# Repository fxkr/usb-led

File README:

USB-RGB-LED
===========

A very simple + cheap + tiny USB-controllable RGB-LED.

Author: Felix Kaiser <felix.kaiser@fxkr.net>
License: GPLv2/GPLv3 (your choice)

Components:

- Board
- Firmware
- Linux tool

We use USB VID/PID f0ss:49d9 (screw you, USB-IF).

Thanks
------

This project is based on:

- Objective Developments V-USB (GPLv2/v3)
  http://www.obdev.at/products/vusb
- Micronucleus' RC Oscillator calibration routine (GPLv2/v3)
  https://github.com/micronucleus/micronucleus/blob/master/firmware/osccalASM.S
- libusb (LGPLv2.1 or later)
  http://libusb.info/
- SparkFuns Eagle Libraries (CC BY-SA 3.0)
  https://github.com/sparkfun/SparkFun-Eagle-Libraries

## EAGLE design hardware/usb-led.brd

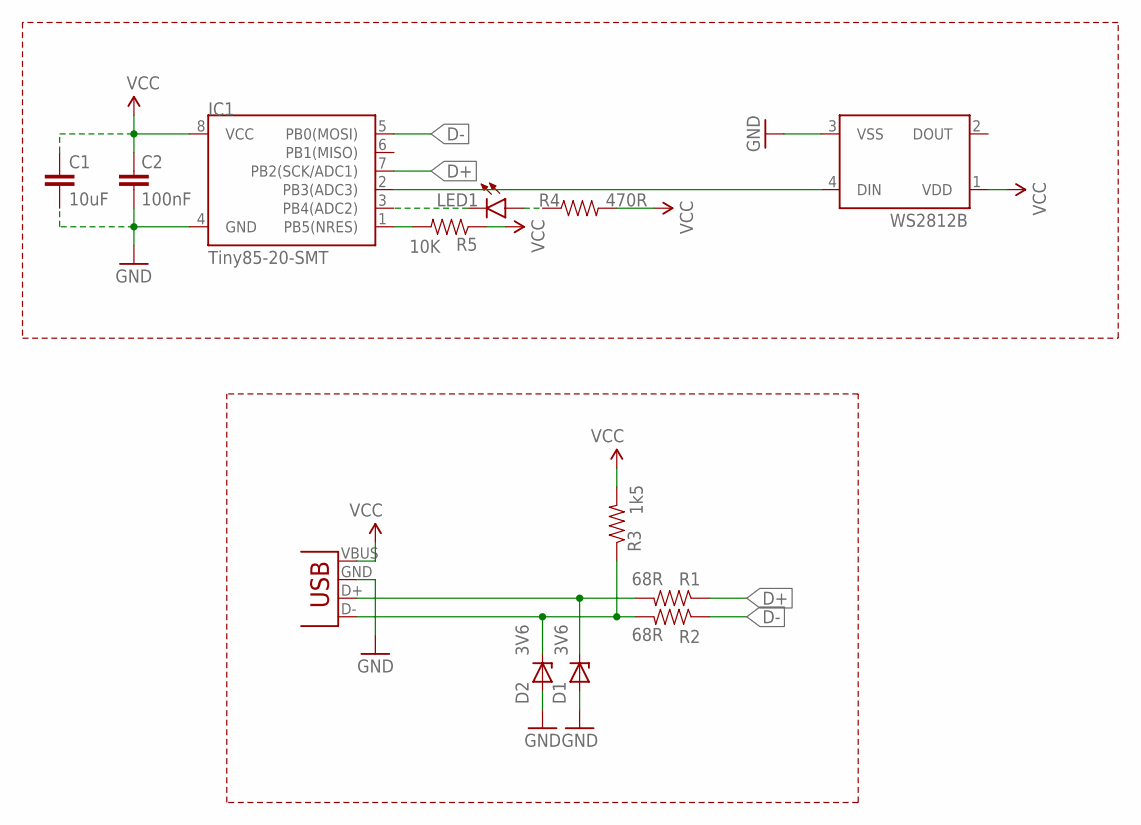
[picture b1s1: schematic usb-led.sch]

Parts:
C1: 10uF; C0805
C2: 100nF; 0805
D1, D2: 3V6; ZD0603
IC1: Tiny85-20-SMT; SO08-EIAJ
LED1: LED0603; LED-0603
R1, R2: 68R; 0603-RES
R3: 1k5; 0603-RES
R4: 470R; 0603-RES
R5: 10K; 0603-RES
USB: USB-A-H
WS2812B: WS2812B

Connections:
C10: IC1.1 (PB5(NRES)), R5.2
D+: IC1.7 (PB2(SCK/ADC1)), R1.1
D-: IC1.5 (PB0(MOSI)), R2.1
DIN: IC1.2 (PB3(ADC3)), WS2812B.4 (DIN)
EXT_D+: D1.K (C), R1.2, USB.D+ (D-)
EXT_D-: D2.K (C), R2.2, R3.1, USB.D- (D+)
GND: C1.2, C2.2, D1.A, D2.A, IC1.4 (GND), USB.GND (VBUS), WS2812B.3 (VSS)
unnamed: IC1.3 (PB4(ADC2)), LED1.C
unnamed: LED1.A, R4.1
VCC: C1.1, C2.1, IC1.8 (VCC), R3.2, R4.2, R5.1, USB.VBUS (GND), WS2812B.1 (VDD)

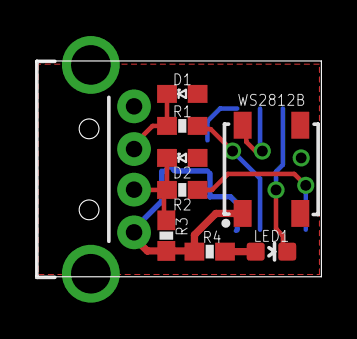
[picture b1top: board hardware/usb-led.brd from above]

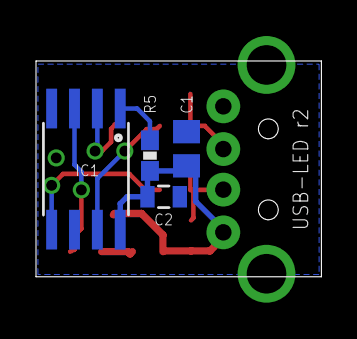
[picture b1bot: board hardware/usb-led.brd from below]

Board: 2 copper layers, 15.9 x 12.0 mm, 13 parts (4 on the bottom side), 10 nets.

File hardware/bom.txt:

Part     Value    Package     Digikey      Qty  Price
IC1      Attiny8  8-SOIC      ATTINY85-20   1   1,36 €
C1       10uF     SMD 0805    1276-1119-1   1   0,17 €
C2       100nF    SMD 0603    399-1096-1-   1   0,09 €
D1, D2   ZD 3V6   SMD 0603    MM3Z3V6T1GO   2   0,13 €
R1, R2   68R      SMD 0603    P68GCT-ND     2   0,09 €
R3       1k5      SMD 0603    MCT0603-1.5   1   0,07 €
R4       470R     SMD 0603    MCT0603-470   1   0,07 €
R5       10K      SMD 0603    MCT0603-10.   1   0,07 €
USB               USB A Male  1175-1008-N   1   0,62 €
WS2812B  WS2812B  5050                      1   0,18 €

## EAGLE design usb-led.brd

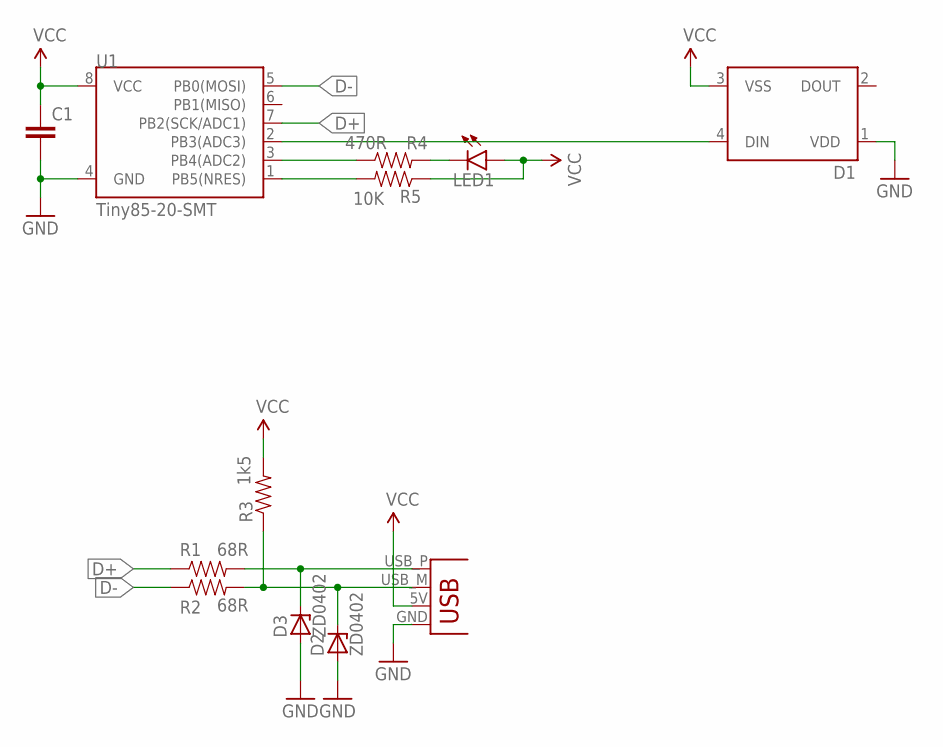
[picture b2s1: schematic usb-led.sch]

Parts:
C1: CAP0805; 0805
D1: WS2812B
D2, D3: ZD0402
JP1: USBPCB; USB-A-PCB
LED1: LED0603; LED-0603
R1, R2: 68R; 0402-RES
R3: 1k5; 0402-RES
R4: 470R; 0603-RES
R5: 10K; 0402-RES
U1: Tiny85-20-SMT; SO08-EIAJ

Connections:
D+: R1.1, U1.7 (PB2(SCK/ADC1))
D-: R2.1, U1.5 (PB0(MOSI))
GND: C1.2, D1.1 (VDD), D2.A, D3.A, JP1.GND, U1.4 (GND); also elsewhere on the board
unnamed 3: D3.K (C), JP1.USB_P (D+), R1.2; also elsewhere on the board
unnamed 4: D2.K (C), JP1.USB_M (D-), R2.2, R3.1; also elsewhere on the board
unnamed: R4.1, U1.3 (PB4(ADC2))
unnamed: LED1.C, R4.2
unnamed: R5.2, U1.1 (PB5(NRES))
unnamed: D1.4 (DIN), U1.2 (PB3(ADC3))
VCC: C1.1, D1.3 (VSS), JP1.5V (VBUS), LED1.A, R3.2, R5.1, U1.8 (VCC); also elsewhere on the board

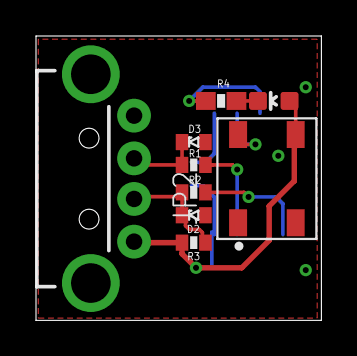
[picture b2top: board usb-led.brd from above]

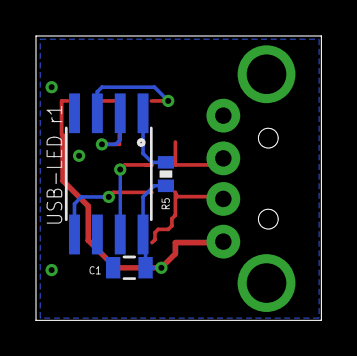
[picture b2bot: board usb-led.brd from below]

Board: 2 copper layers, 15.9 x 15.8 mm, 12 parts (3 on the bottom side), 10 nets.

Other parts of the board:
JP2: USB-A-H

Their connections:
GND: JP2.GND; also elsewhere on the board
unnamed 3: JP2.D+; also elsewhere on the board
unnamed 4: JP2.D-; also elsewhere on the board
VCC: JP2.VBUS; also elsewhere on the board

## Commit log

2014-07-19 Add .gitignore
2014-07-19 Import schematic + board
2014-07-19 Forgot two 3.6V Z-Diodes
2014-10-03 Use real USB connector, not PCB-trace-based one
    OSHPark PCBs are not thick enoguh (1.5mm, not 2.4mm)
2014-10-03 Add r1 label
2014-10-04 Fix silkscreen
2014-12-12 Move brd/sch to hardware/
2014-12-12 Import firmware
2014-12-13 Firmware: Split up "Set RGB" cmd, add apply cmd
2014-12-13 Import command line tool
2014-12-13 Add README and licenses (GPLv2/3)
2014-12-13 Hardware: revision 2
    - Fix: WS2812Bs DIN/DOUT pins were swapped. This was a bug in
    SparkFuns eagle library (fixed in latest version).
    - Smaller board: border now cuts through USB plug mounting via.
    OSHPark support said it's fine. We'll see.
    If it doesn't work, I'll have to either use the larger board size,
    find an (expensive) SMD male USB A connector or use a PCB connector
2014-12-13 Firmware: check checksum of USB packets
    This only checks USB Control Transfer packets.
    In particular, it doesn't check packets v-usb handles internally.
    But it's better than nothing.
2014-12-14 Firmware: -std=c99
2014-12-14 Firmware: add time measurement
    We now count the number of milliseconds since boot.
    As a test, we blink the status LED every second.
2014-12-14 Firmware: Add comment
2014-12-14 Firmware: on bootup, blink twice instead of once
    Makes it distinguishable from the new once-per-second blinking.
2014-12-14 Hardware: rename parts
2014-12-14 Hardware: more space for the Zener diodes
    Their case is a a little bit larger than the normal 0603 footprint.
2014-12-15 Firmware: Add gamma correction
2014-12-15 Hardware: add BOM
    Please don't actually buy single 0603 100nF capacitors.
2014-12-16 Firmware/Tool: 16 bit colors + better gamma table
2014-12-16 Firmware: add show-size/show-bss to Makefile
2014-12-16 Firmware: Fix: use _unsigned_ char for gamma table
2014-12-16 Firmware/Tool: Add fading
2014-12-16 README: Actually, we're not using docopt.c
2014-12-16 Firmware/Tool: Make fade speed configurable
2014-12-16 Firmware: allow stopping fade by setting rate to 0
2014-12-16 Firmware/Tool: Add support for blinking
2014-12-16 Firmware: restore brightness when blinking ends
2014-12-16 Firmware/Tool: Status led: Add off/on/blink choice
2014-12-17 Firmware: Fix: add missing return in a case branch
2014-12-18 Gamma: Add gamma correction table generator script
    Somewhat hacked together, but it's a one-shot thing.
2015-01-08 Firmware: minor fix in a comment
2015-02-22 Gamma: fix typo in comment
2015-08-03 Firmware: Make flashing more robust with -B 8
2015-08-28 Firmware: Fix comment explaining sbrs instruction

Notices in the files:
parts and their libraries:
SparkFun-DigitalIC: Licensing: Creative Commons ShareAlike 4.0 International - https://creativecommons.org/licenses/by-sa/4.0
